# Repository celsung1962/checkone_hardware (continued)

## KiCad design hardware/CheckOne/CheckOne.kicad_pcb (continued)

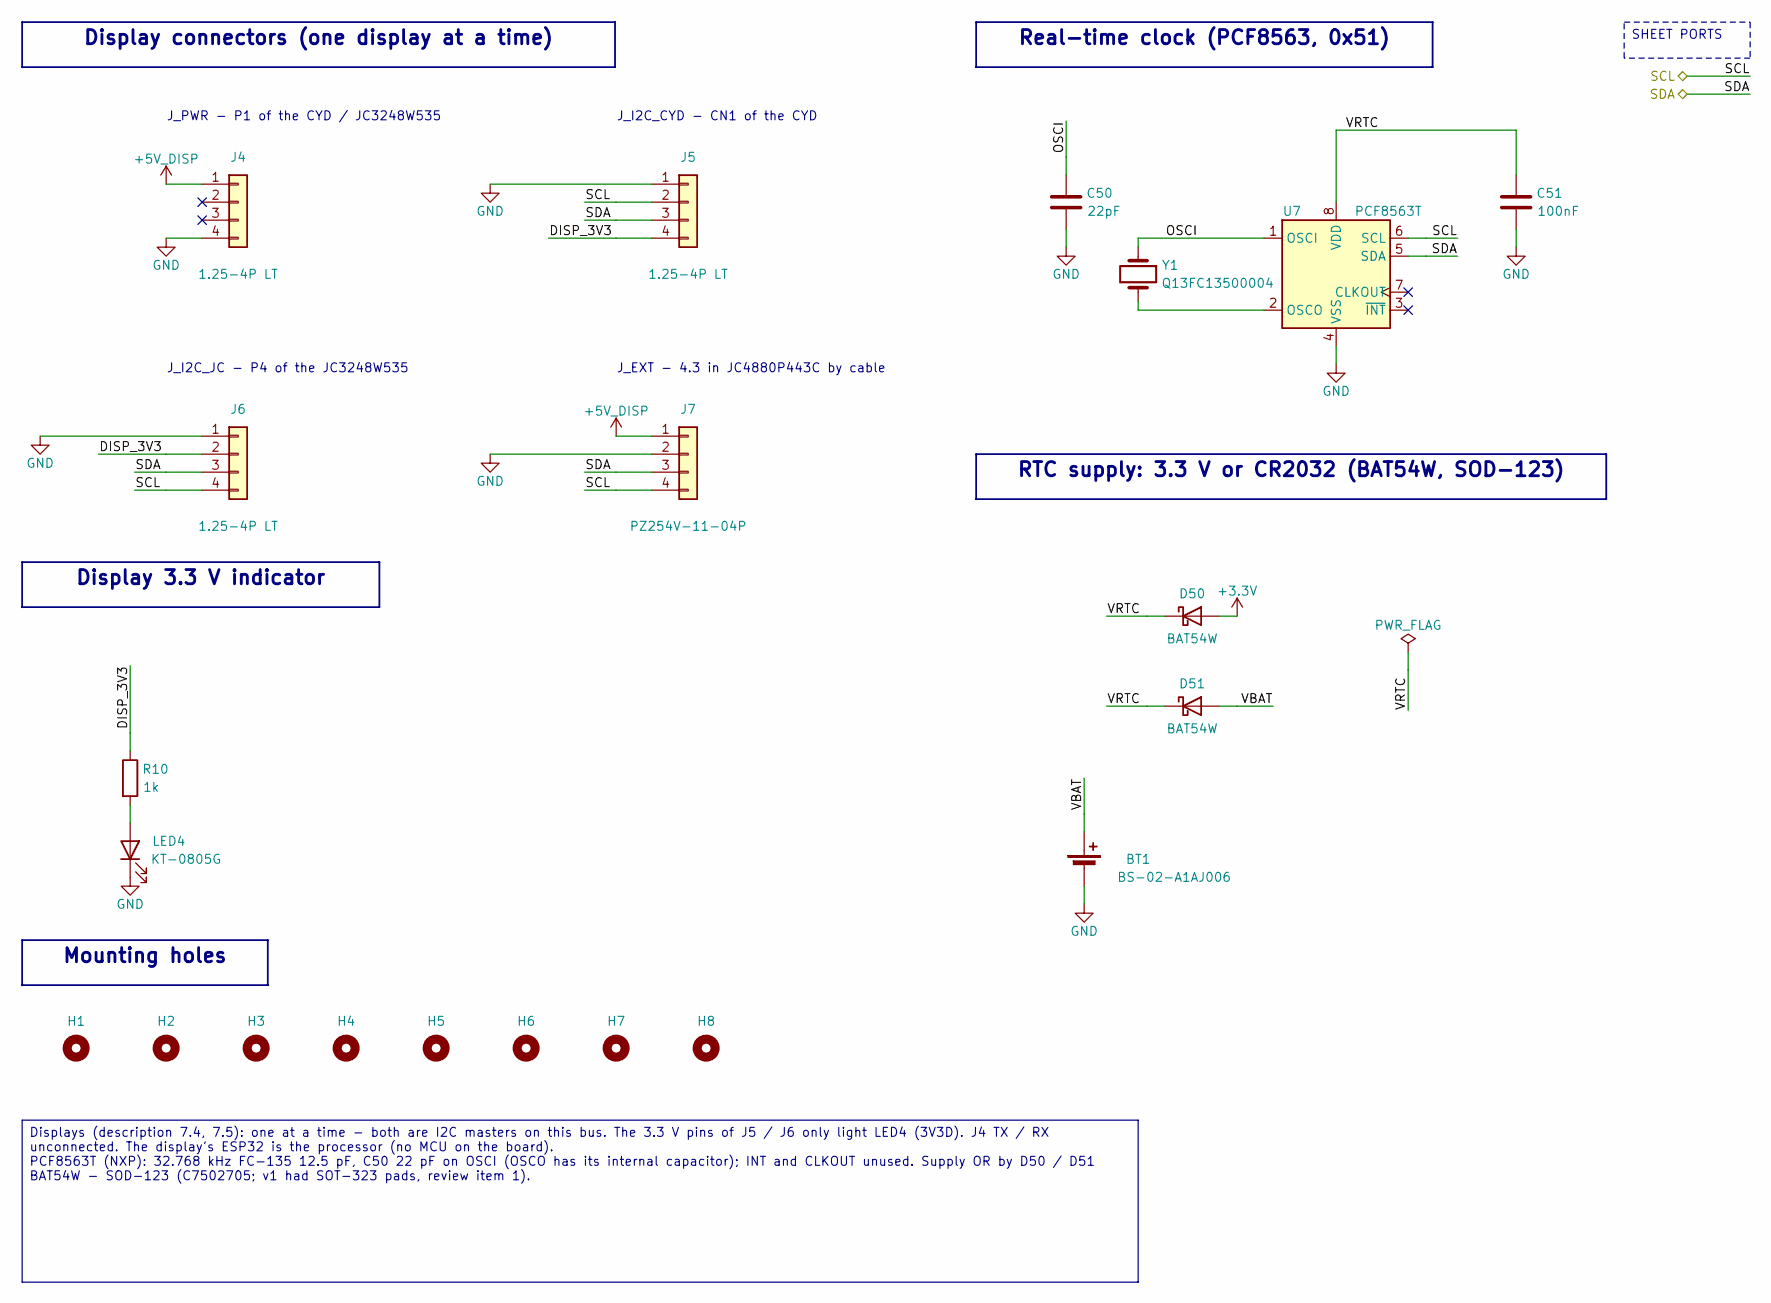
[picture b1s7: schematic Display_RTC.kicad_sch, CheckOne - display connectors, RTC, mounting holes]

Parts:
BT1: BS-02-A1AJ006; LCSC C964745
C50: 22pF; C_0603_1608Metric; LCSC C1653
C51: 100nF; C_0603_1608Metric; LCSC C14663
D50, D51: BAT54W; D_SOD-123; LCSC C7502705
H1, H2, H3, H4: M3 board; MountingHole_3.2mm_M3
H5, H6, H7, H8: M3 display spacer; MountingHole_3.2mm_M3
J4, J5, J6: 1.25-4P LT; Molex_PicoBlade_53398-0471_1x04-1MP_P1.25mm_Vertical; LCSC C668611
J7: PZ254V-11-04P; PinHeader_1x04_P2.54mm_Vertical; LCSC C2691448
LED4: KT-0805G; LED_0805_2012Metric; LCSC C2297
R10: 1k; R_0603_1608Metric; LCSC C21190
U7: PCF8563T; SOIC-8_3.9x4.9mm_P1.27mm; LCSC C7440
Y1: Q13FC13500004; Crystal_SMD_3215-2Pin_3.2x1.5mm; LCSC C32346

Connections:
+3.3V: D50.2 (A); also elsewhere on the board
+5V_DISP: J4.1, J7.1; also elsewhere on the board
/Display_RTC/DISP_3V3: J5.4, J6.2, R10.1
/Display_RTC/OSCI: C50.1, U7.1 (OSCI), Y1.1
/Display_RTC/VBAT: BT1.1 (+), D51.2 (A)
/Display_RTC/VRTC: C51.1, D50.1 (K), D51.1 (K), U7.8 (VDD)
/SCL: J5.2, J6.4, J7.4, U7.6 (SCL); also elsewhere on the board
/SDA: J5.3, J6.3, J7.3, U7.5 (SDA); also elsewhere on the board
GND: BT1.2 (-), C50.2, C51.2, J4.4, J5.1, J6.1, J7.2, LED4.1 (K), U7.4 (VSS); also elsewhere on the board
unnamed: LED4.2 (A), R10.2
unnamed: U7.2 (OSCO), Y1.2

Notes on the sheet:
Display connectors (one display at a time)
J_PWR - P1 of the CYD / JC3248W535
J_I2C_CYD - CN1 of the CYD
J_I2C_JC - P4 of the JC3248W535
J_EXT - 4.3 in JC4880P443C by cable
Display 3.3 V indicator
Real-time clock (PCF8563, 0x51)
RTC supply: 3.3 V or CR2032 (BAT54W, SOD-123)
Mounting holes
Displays (description 7.4, 7.5): one at a time - both are I2C masters on this bus. The 3.3 V pins of J5 / J6 only light LED4 (3V3D). J4 TX / RX unconnected. The display's ESP32 is the processor (no MCU on the board). PCF8563T (NXP): 32.768 kHz FC-135 12.5 pF, C50 22 pF on OSCI (OSCO has its interna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
SHEET PORTS

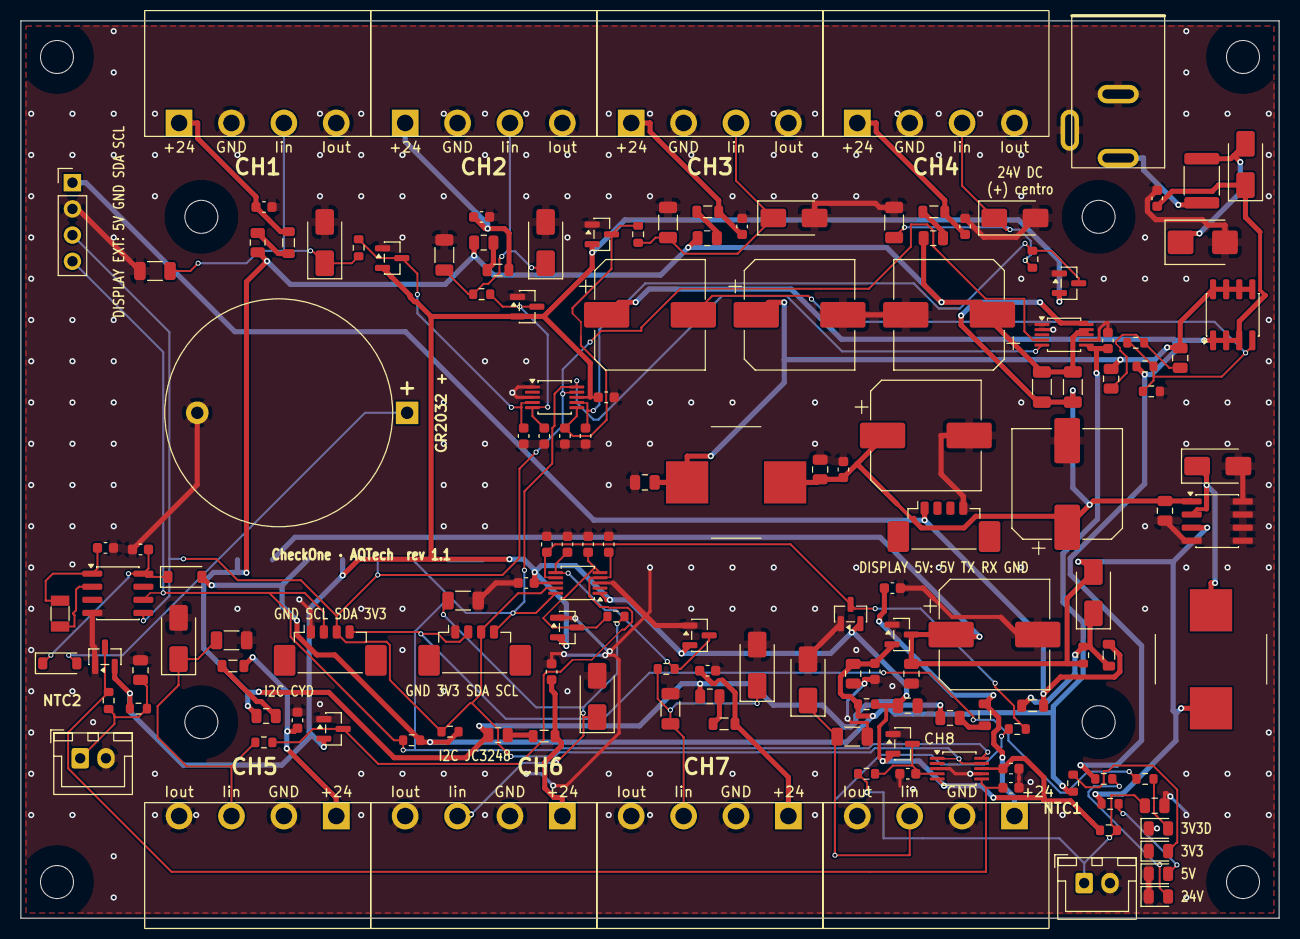
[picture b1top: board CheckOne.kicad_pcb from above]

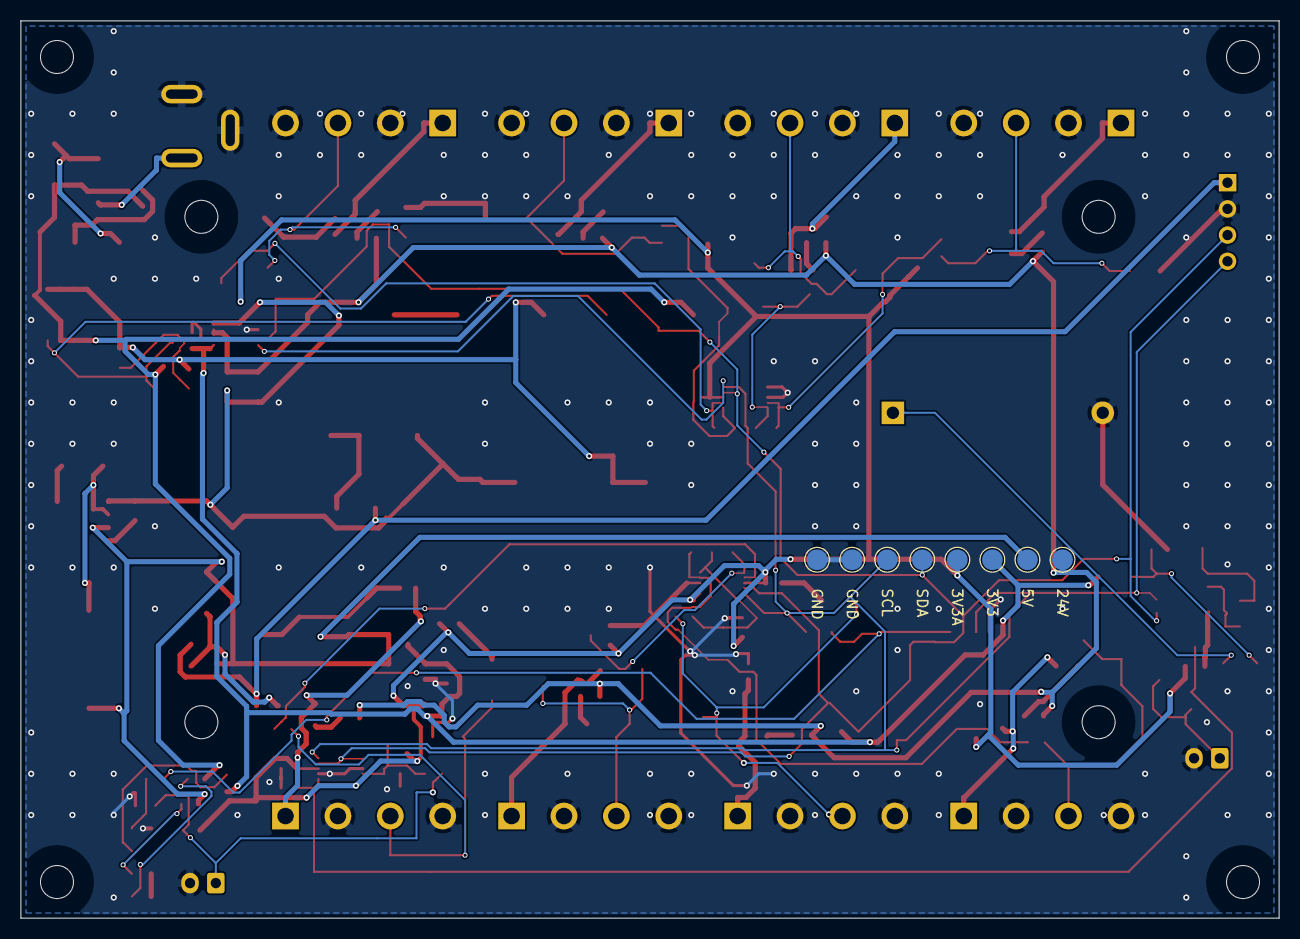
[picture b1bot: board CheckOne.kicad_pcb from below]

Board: 2 copper layers, 122.0 x 87.0 mm, 166 parts (8 on the bottom side), 62 nets.

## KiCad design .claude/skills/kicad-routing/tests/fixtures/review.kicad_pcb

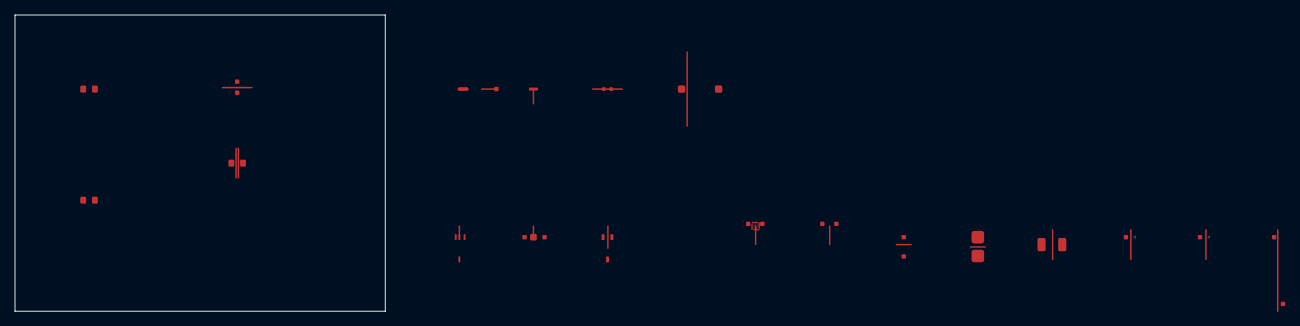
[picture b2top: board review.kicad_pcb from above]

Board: 4 copper layers, 50.0 x 40.0 mm, 29 parts (0 on the bottom side), 9 nets.

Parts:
P3: 10k; R_0603_1608Metric
P4: 10k; R_1206_3216Metric
Q1, Q2: 10k; QFN_test
TP2, TP3, TP4, TP5, TP6, TP7, TP8, TP9, TP10, TP11, TP12, TP13, TP14, TP15, TP16, TP17, TP18: 10k; TestPoint
U1, U2: 10k; R_0603_1608Metric
U3, U4, U5, U6, U7: 10k; TestPoint
Y1: 10k; Crystal_SMD_3225_4Pin

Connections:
A: P3.1, U1.1, U2.1
B: P3.2, U1.2, U2.2
EXIT_NB1: Q1.1, Q2.1
EXIT_NB2: Q1.3, Q1.4, Q2.2, Q2.3
GAP_A: P4.1, TP11.1, TP13.1, TP15.1, TP16.1, TP17.1
GAP_B: P4.2, TP12.1, TP14.1, TP18.1
POUR_FL1: TP7.1, TP9.1
POUR_FL2: TP8.1, TP10.1
XTAL: Y1.1, Y1.2

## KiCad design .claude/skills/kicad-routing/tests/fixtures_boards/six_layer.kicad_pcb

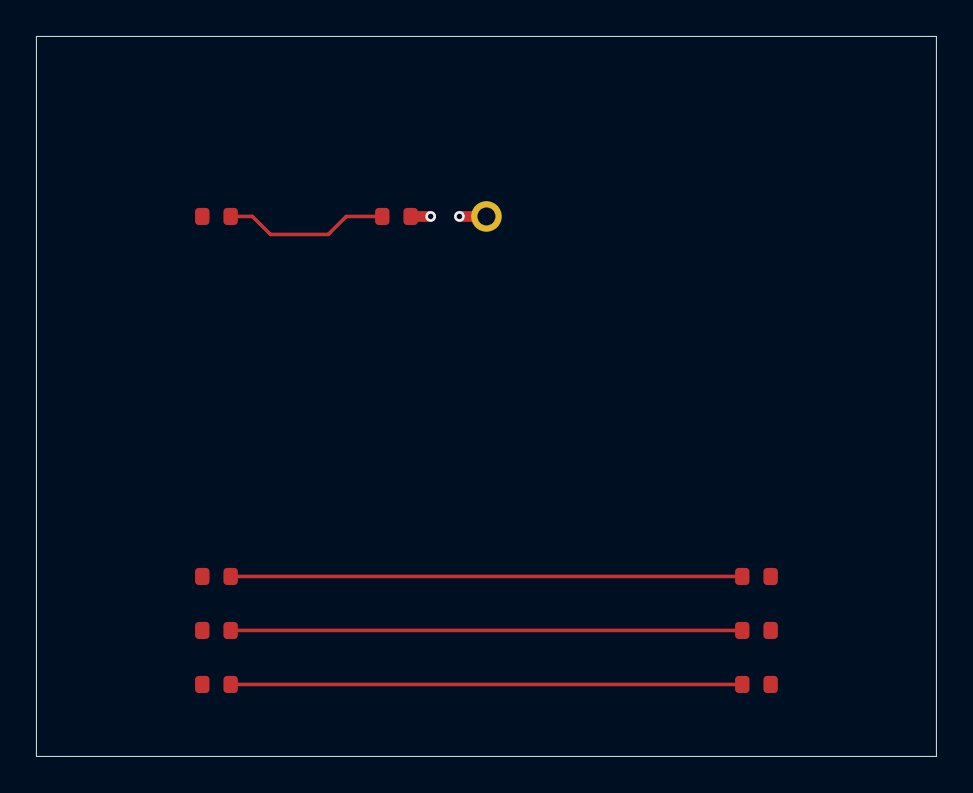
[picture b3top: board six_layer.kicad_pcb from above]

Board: 6 copper layers, 50.0 x 40.0 mm, 10 parts (0 on the bottom side), 6 nets.

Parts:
J1: Conn; PinHeader_1x01_P2.54mm_Vertical
R1, R2, R3, R4, R5, R6, R7, R8: 10k; R_0603_1608Metric
TP1: TP; TestPoint

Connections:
+3.3V: J1.1, R2.2
BUS_CLK: R5.2, R8.1
BUS_D0: R3.2, R6.1
BUS_D1: R4.2, R7.1
GND: R1.1, R3.1, R4.1, R5.1, R6.2, R7.2, R8.2
SIG: R1.2, R2.1

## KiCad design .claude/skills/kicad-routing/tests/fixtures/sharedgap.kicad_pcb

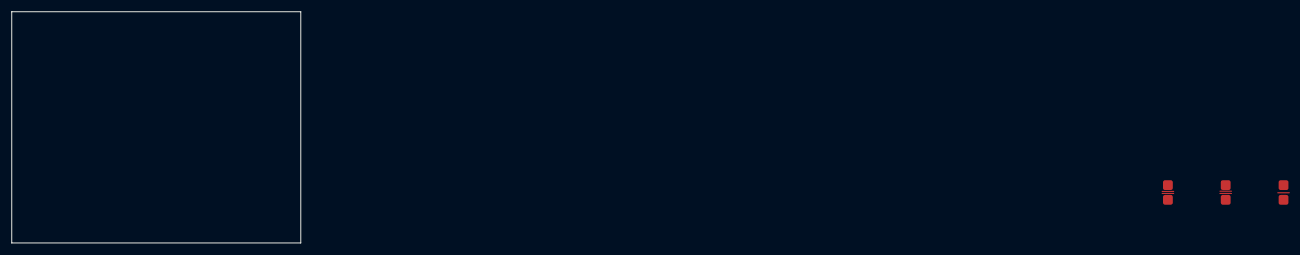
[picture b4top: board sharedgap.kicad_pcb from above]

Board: 4 copper layers, 50.0 x 40.0 mm, 6 parts (0 on the bottom side), 2 nets.

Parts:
H1, H2, H3, H4, H5, H6: 10k; TestPoint

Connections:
A: H1.1, H3.1, H5.1
B: H2.1, H4.1, H6.1

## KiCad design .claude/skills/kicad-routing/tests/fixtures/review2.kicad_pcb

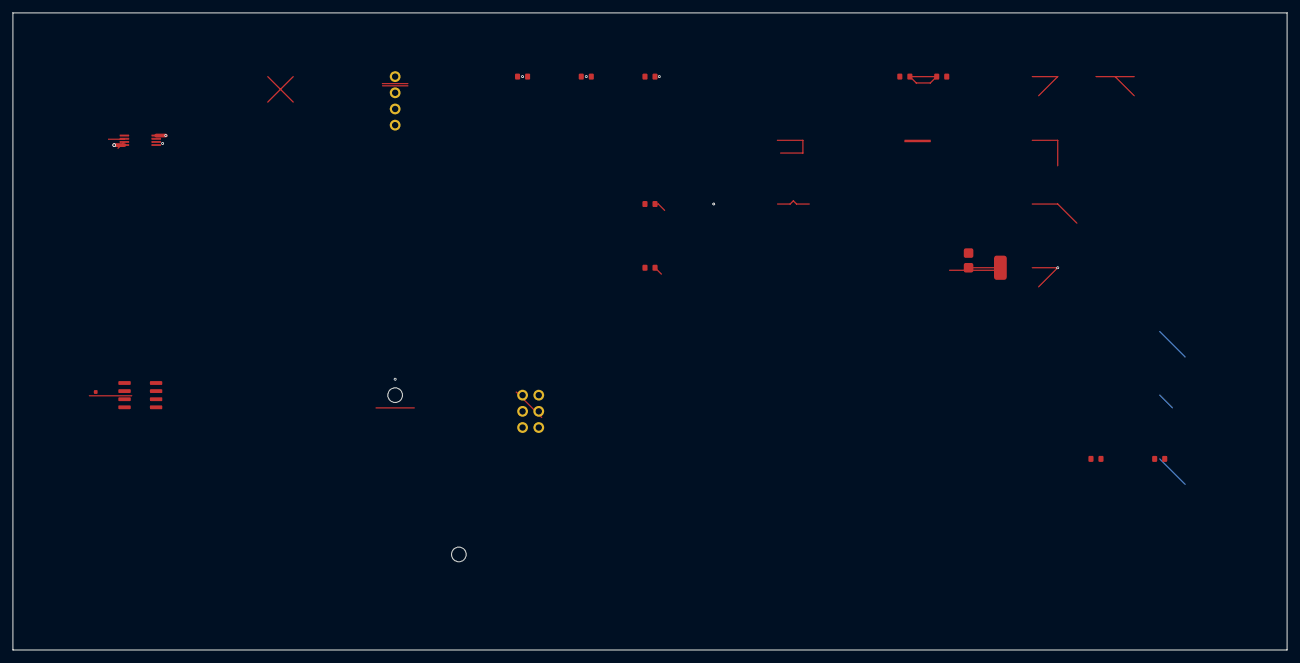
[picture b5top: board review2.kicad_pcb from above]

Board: 4 copper layers, 200.0 x 100.0 mm, 17 parts (0 on the bottom side), 3 nets.

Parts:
H30, H31: x; MountingHole_2.3mm_M2
J5: x; PinHeader_1x04_P2.54mm_Vertical
J6: x; PinHeader_2x03_P2.54mm_Vertical
M50, M51: x; R_0603_1608Metric
Q30: x; SOT-223
R20, R21, R22, R23, R24, R26, R27: x; R_0603_1608Metric
TP41: x; TestPoint_Pad_test
U20: x; FinePitch_test
U40: x; SOIC-8_test

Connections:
GND: U20.4, U20.8
LOOPN: R23.2, R24.1
THRUL: Q30.2, Q30.4

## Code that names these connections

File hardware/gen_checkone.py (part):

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        two(sh, c, "+3.3VA", "GND")
    section(sh, "NTC inputs and NTC ADC U6 (0x4A)", (99.06, 22.86))
    u6 = ic(sh, "ADS1115IDGSR", "U6", (226.06, 93.98))
    sh.label(u6, "4", "NTC1_ADC")
    sh.label(u6, "6", "NTC2_ADC")
    for pin, net in (("5", "+3.3VA"), ("7", "GND")):      # AIN1 reads the divider supply, AIN3 unused (grounded)
        pp = sh.pt(u6, pin)
        sh.wire(pp, (pp[0] - 22.86, pp[1]))
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                sh.label(j, pin, net, kind="global" if net in ("SDA", "SCL") else "local", stub=5.08)
    section(sh, "Display 3.3 V indicator", (15.24, 91.44))
    r10 = part(sh, "R:1k", "R10", (30.48, 121.92))
    sh.label(r10, "1", "DISP_3V3")
    led, _ = sh.drop(sh.pt(r10, "2"), f"{P}:KT-0805G", "LED4", direction="down", gap=2.54, pin1="2", end="GND")

    section(sh, "Real-time clock (PCF8563, 0x51)", (149.86, 15.24))
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    sh.wire(osci, (ya[0], osci[1]), ya) if ya[1] < yb[1] else sh.wire(osci, (yb[0], osci[1]), yb)
    sh.wire(osco, (yb[0], osco[1]), yb) if ya[1] < yb[1] else sh.wire(osco, (ya[0], osco[1]), ya)
    c50 = part(sh, "C:22pF", "C50", (162.56, 40.64))
    sh.label(c50, "1", "OSCI")
    sh.power(c50, "2", "GND", stub=2.54)
    name(sh, (176.53, osci[1]), "OSCI")
    sh.power(u7, "4", "GND", stub=2.54)
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    d50 = sh.place(f"{P}:BAT54W", "D50", (180.34, y))
    d51 = sh.place(f"{P}:BAT54W", "D51", (180.34, y + 12.7))
    for d, a_net in ((d50, "+3.3V"), (d51, None)):
        sh.label(d, "1", "VRTC")
        if a_net:
            sh.power(d, "2", a_net, stub=2.54)
        else:
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    sh.label(bt, "1", "VBAT")
    sh.power(bt, "2", "GND", stub=2.54)
    f = sh.place("power:PWR_FLAG", f"#FLG{sh.tag}02", (210.82, 104.14), value="PWR_FLAG")
    sh.label(f, "1", "VRTC")
    section(sh, "Mounting holes", (15.24, 144.78))
    for i in range(8):
        h = sh.place(f"{P}:MountingHole", f"H{i + 1}", (22.86 + i * 12.7, 160.02),
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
